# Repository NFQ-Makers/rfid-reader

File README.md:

RFID Reader
===========

A not so simple 125KHz rfid reader based on a ATTiny and EM4095

Build around a single timer (Timer0), uses two interrupts pin change and INT0
Manchester code decoding based on Timing approach. Base clock 16.5MHz.

Input
-------
- **PB2** - Input of Card data (after EM)

Outputs
-------
- **PB1** - EM4095 disable / Red led
- **PB0** - Green led

Quite interseting
------
This device tries to calibrate itself to 16.5MHz by measuring usb packet lenght. It also stores its last calibration
value to EEPROM byte address 0 (first byte as this can be read by avrdude)

Also never compile this with optimization level -O3 as USB will not work. -Os (size) seems to be ok

Makefile
------
For convinience there is a make file with instructions:
- **make** - compiles the compileables
- **make flash** - flashes flash with a flash file
- **make fuse** - tries to fuse the fuses
- **make install** - compiles, flashes, fuses

PCB
------
Double layer SMD in KiCad format

AVR Memory Usage
------
```
Device: attiny85

Program:    2456 bytes (30.0% Full)
(.text + .data + .bootloader)

Data:         70 bytes (13.7% Full)
(.data + .bss + .noinit)
```
---
**Thanks to:**

- [Vassilis Serasidis](http://www.serasidis.gr/circuits/RFID_reader/125kHz_RFID_reader.htm) - Manchester code ideas
- [V-USB](http://www.obdev.at/products/vusb/index.html) - Software USB support :)

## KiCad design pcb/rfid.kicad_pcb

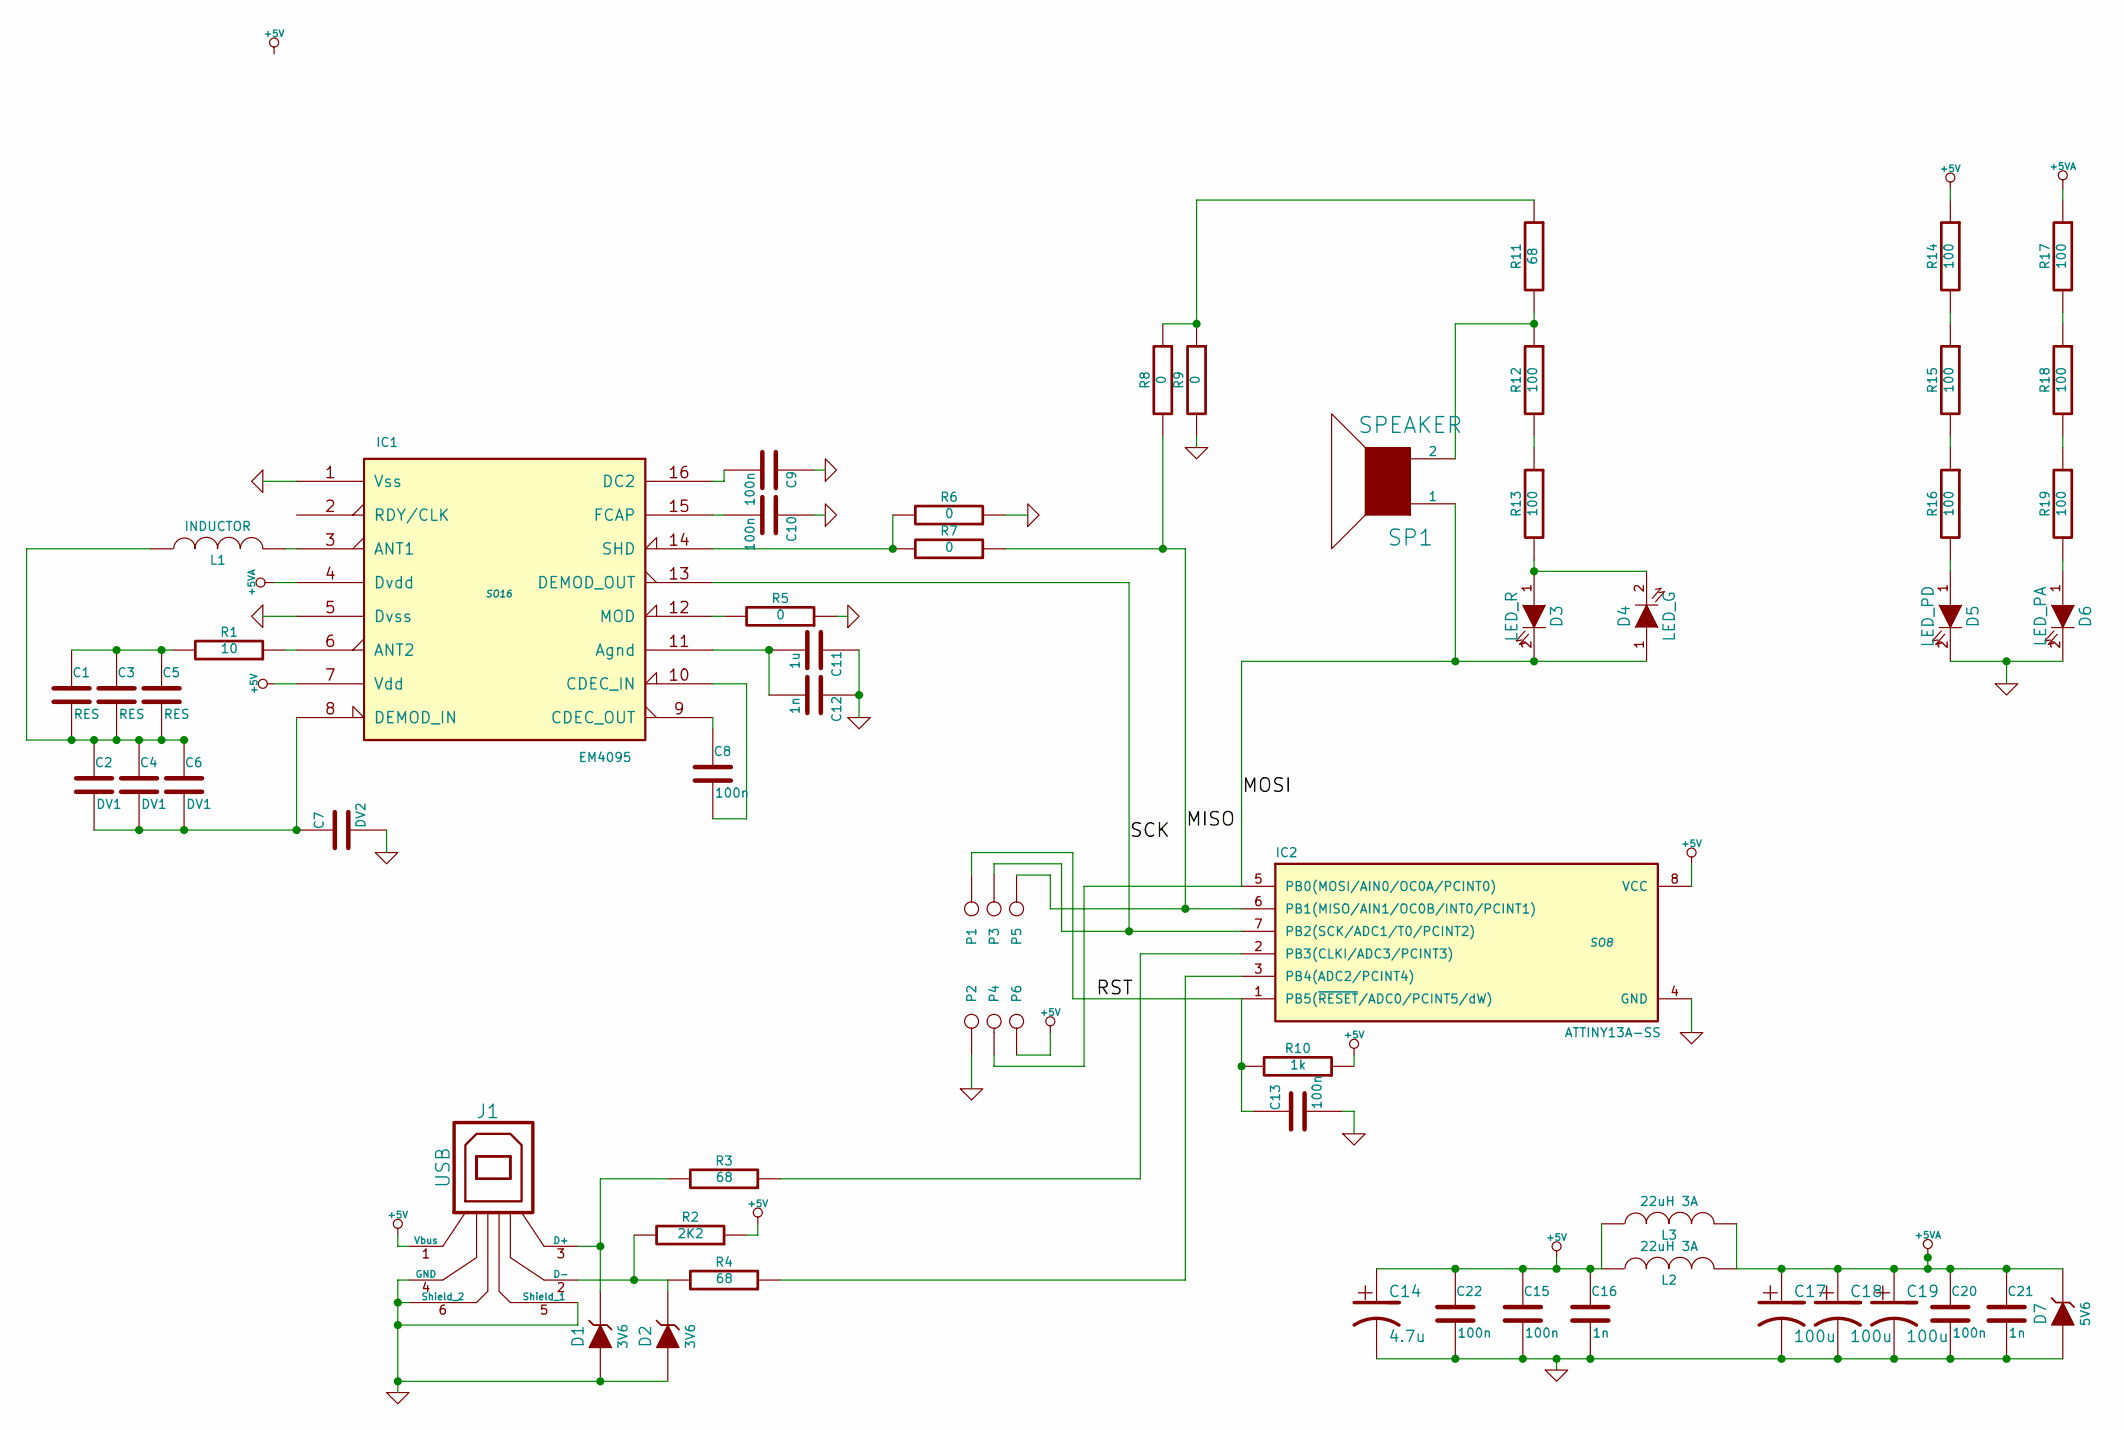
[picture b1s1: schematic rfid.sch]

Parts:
C1, C3, C5: RES
C2, C4, C6: DV1
C7: DV2
C8, C9, C10, C13, C15, C20, C22: 100n
C11: 1u
C12, C16, C21: 1n
C14: 4.7u
C17, C18, C19: 100u
D1, D2: 3V6
D3: LED_R
D4: LED_G
D5: LED_PD
D6: LED_PA
D7: 5V6
IC1: EM4095; SO16
IC2: ATTINY13A-SS; SO8
J1: USB
L1: INDUCTOR
L2, L3: 22uH 3A
P1, P2, P3, P4, P5, P6: CONN_1
R1: 10
R2: 2K2
R3, R4, R11: 68
R5, R6, R7, R8, R9: 0
R10: 1k
R12, R13, R14, R15, R16, R17, R18, R19: 100
SP1: SPEAKER

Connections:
+5V: C14.1, C15.1, C16.1, C22.1, IC1.7 (Vdd), IC2.8 (VCC), J1.1 (Vbus), L2.1, L3.1, P6.1, R2.1, R10.1, R14.1
+5VA: C17.1, C18.1, C19.1, C20.1, C21.1, D7.2 (K), IC1.4 (Dvdd), L2.2, L3.2, R17.1
/MISO: IC2.6 (PB1(MISO/AIN1/OC0B/INT0/PCINT1)), P5.1, R7.1, R8.2
/MOSI: D3.2 (K), D4.1 (A), IC2.5 (PB0(MOSI/AIN0/OC0A/PCINT0)), P4.1, SP1.1
/RST: C13.1, IC2.1 (PB5(~RESET~/ADC0/PCINT5/dW)), P1.1, R10.2
/SCK: IC1.13 (DEMOD_OUT), IC2.7 (PB2(SCK/ADC1/T0/PCINT2)), P3.1
GND: C7.2, C9.1, C10.1, C11.1, C12.1, C13.2, C14.2, C15.2, C16.2, C17.2, C18.2, C19.2, C20.2, C21.2, C22.2, D1.1 (A), D2.1 (A), D5.2 (K), D6.2 (K), D7.1 (A), IC1.1 (Vss), IC1.5 (Dvss), IC2.4 (GND), J1.4 (GND), J1.5 (Shield_1), J1.6 (Shield_2), P2.1, R5.1, R6.1, R9.2
unnamed: R17.2, R18.1
unnamed: R14.2, R15.1
unnamed: D6.1 (A), R19.2
unnamed: D5.1 (A), R16.2
unnamed: IC1.14 (SHD), R6.2, R7.2
unnamed: R15.2, R16.1
unnamed: R18.2, R19.1
unnamed: IC2.3 (PB4(ADC2/PCINT4)), R4.1
unnamed: IC2.2 (PB3(CLKI/ADC3/PCINT3)), R3.1
unnamed: C11.2, C12.2, IC1.11 (Agnd)
unnamed: C8.1, IC1.9 (CDEC_OUT)
unnamed: R11.2, R12.1, SP1.2
unnamed: R8.1, R9.1, R11.1
unnamed: R12.2, R13.1
unnamed: D3.1 (A), D4.2 (K), R13.2
unnamed: C9.2, IC1.16 (DC2)
unnamed: C8.2, IC1.10 (CDEC_IN)
unnamed: D1.2 (K), J1.3 (D+), R3.2
unnamed: C10.2, IC1.15 (FCAP)
unnamed: IC1.12 (MOD), R5.2
unnamed: IC1.6 (ANT2), R1.1
unnamed: IC1.3 (ANT1), L1.2
unnamed: C1.1, C3.1, C5.1, R1.2
unnamed: C2.2, C4.2, C6.2, C7.1, IC1.8 (DEMOD_IN)
unnamed: C1.2, C2.1, C3.2, C4.1, C5.2, C6.1, L1.1
unnamed: D2.2 (K), J1.2 (D-), R2.2, R4.2

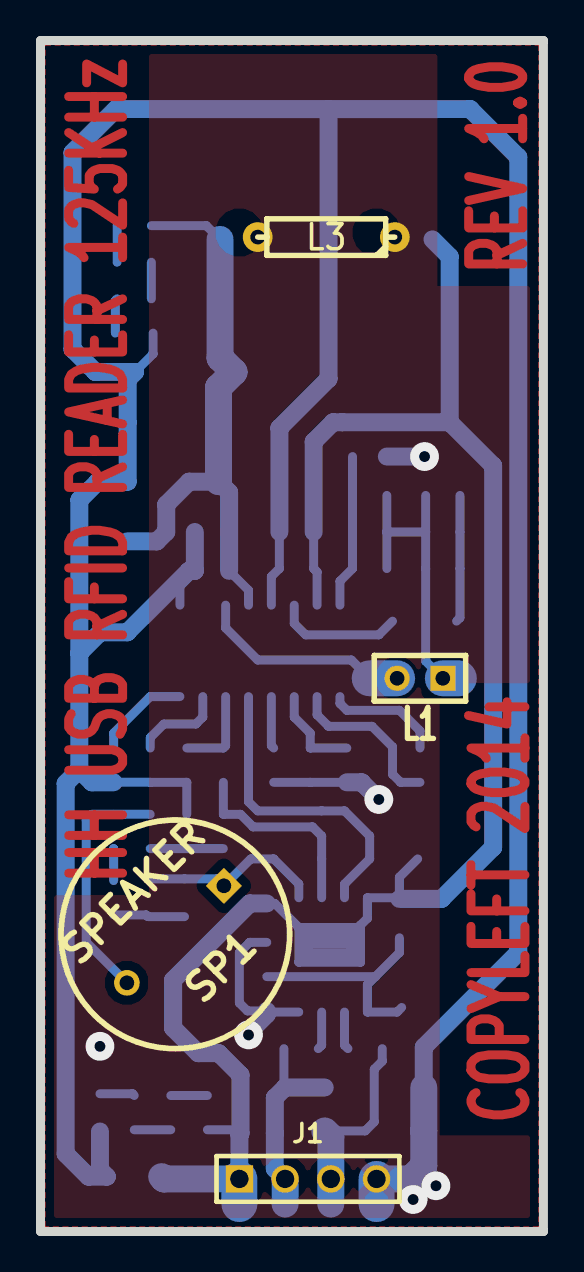
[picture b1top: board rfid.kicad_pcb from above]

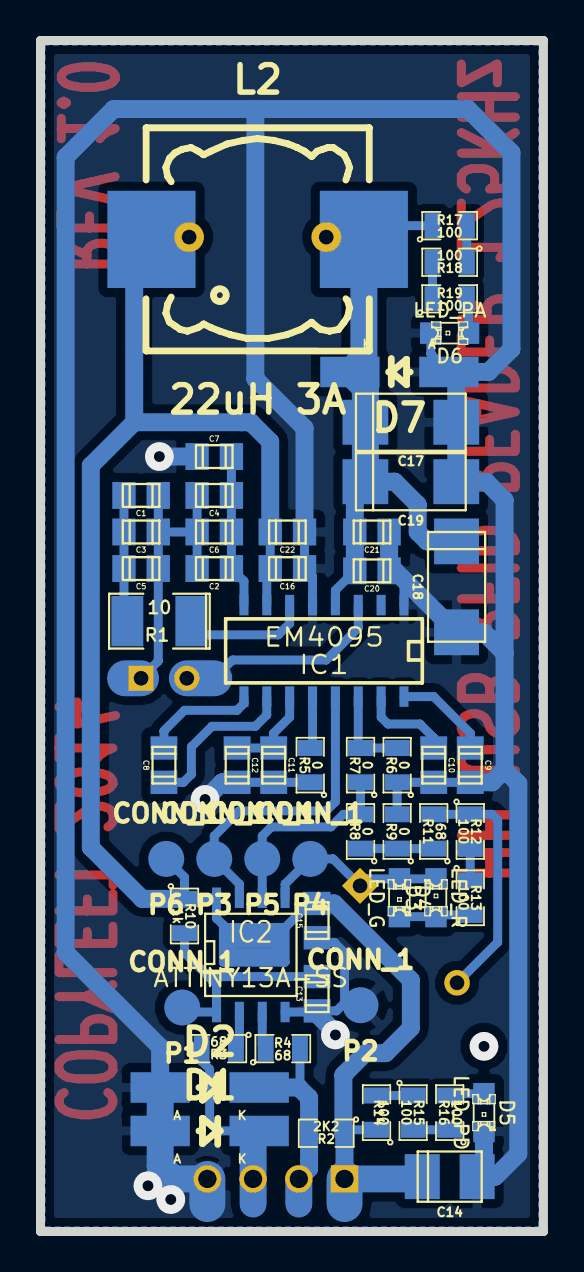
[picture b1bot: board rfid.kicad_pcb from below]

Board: 2 copper layers, 27.9 x 66.2 mm, 61 parts (57 on the bottom side), 33 nets.

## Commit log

2014-07-18 copying reader from project https://github.com/joinedforces/nekvailas_stalas
2014-07-18 adding USB stuff to use with v-usb
2014-09-12 replaced RF frontend with EM4095
2014-09-20 connecting attiny13 and adding schematics png
2014-09-20 associating footprints and minor schematics changes
2014-09-26 starting new pcb routing
2014-10-13 routing pcb with only few GND left unconnected
2014-10-14 adding ISP pads to schematics
2014-10-14 finalising pcb routing
2014-10-16 fixing some library paths
2014-10-16 shrinking PCB and adding BOM
2014-10-26 Updated RF reader for attiny and EM frontend
2014-10-26 README update
2014-10-26 Added mem info
2014-10-26 Markdown changes
2014-10-26 Fixed idents
2014-10-29 Increased different card numbers support
2014-11-06 Experimental usb support
2014-11-06 Finished USB support for attiny85
2014-11-07 Added todo regarding USB
2014-11-07 us not ms
2014-11-20 Some major changes
    Reduced base clock to 16.5MHz
    Added auto tune rutines for OSCCAL calibration
    Added key release event after each character
    Added leading 0's to the card number
    Delay changes (needs more work)
    Removed tune target from Makefile (as its not needed anymore)

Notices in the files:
pcb/rfid.kicad_pcb:
COPYLEFT 2014
